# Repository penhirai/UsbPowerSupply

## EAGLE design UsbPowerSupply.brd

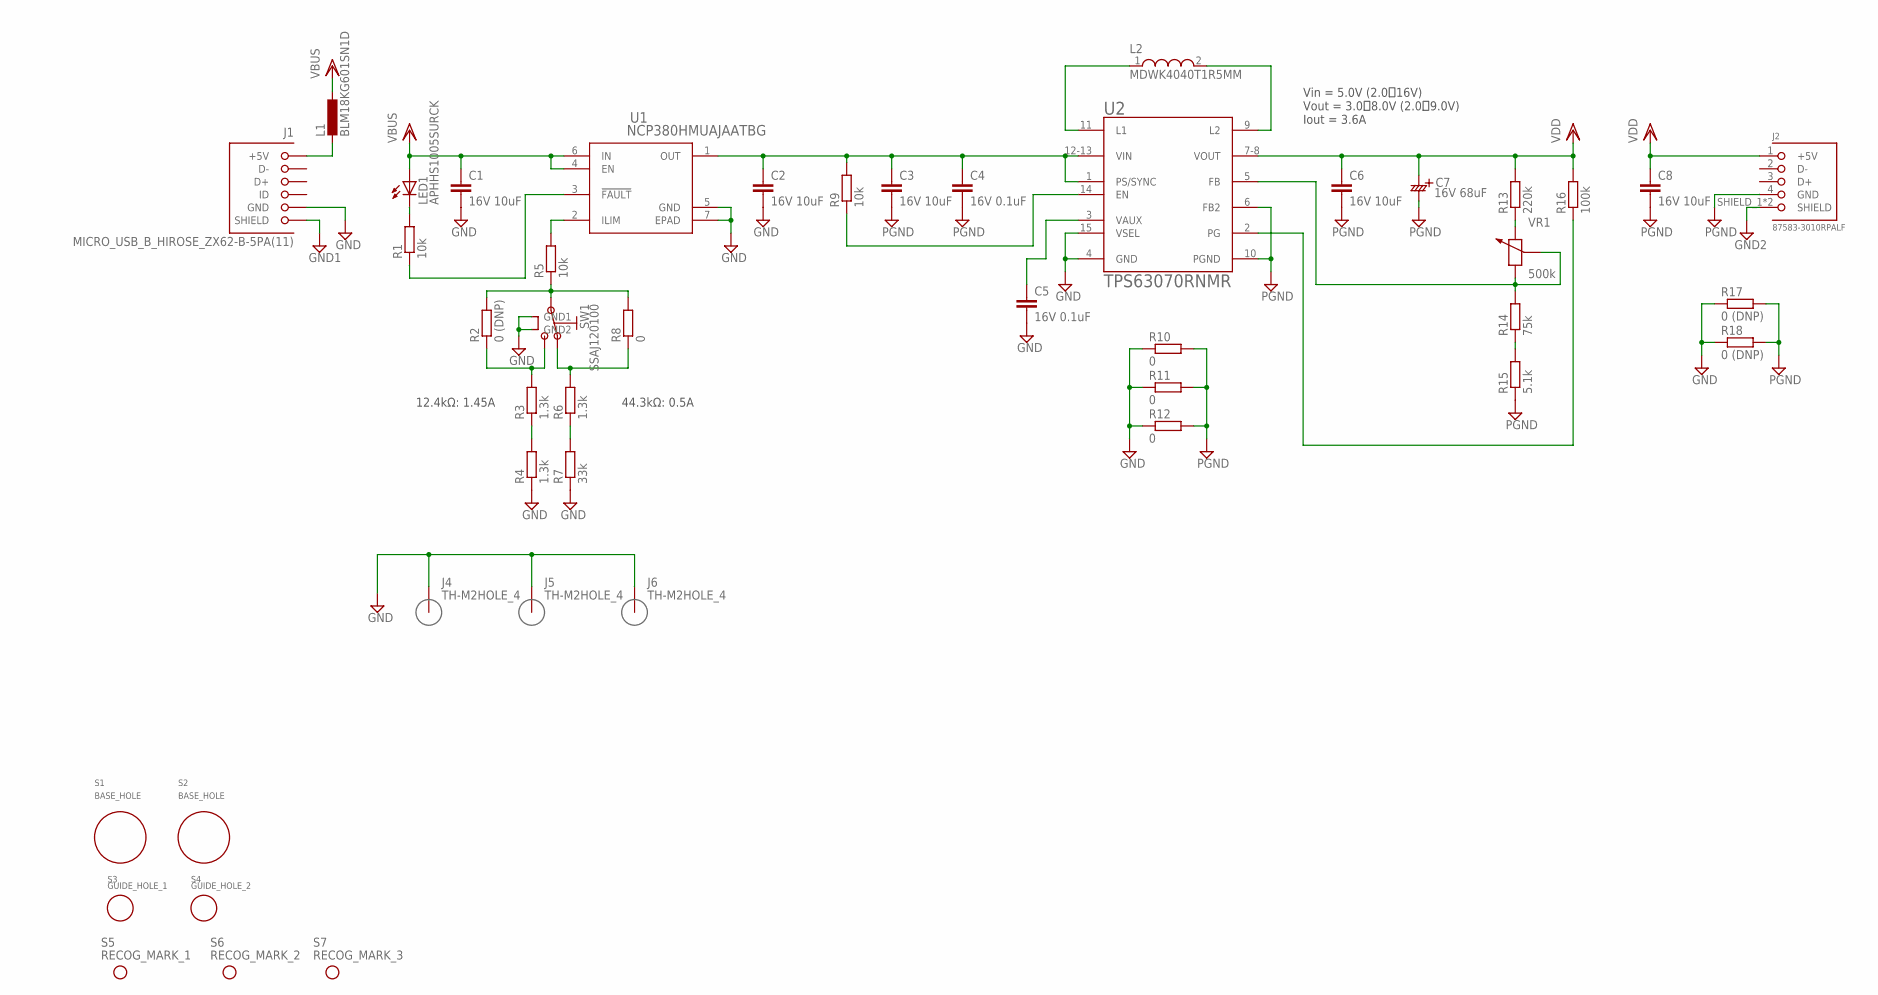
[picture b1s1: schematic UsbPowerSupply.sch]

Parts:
C1, C2, C3, C6, C8: 16V 10uF; C0603M
C4, C5: 16V 0.1uF; C0402M
C7: 16V 68uF; EEFCX_7343
J1: MICRO_USB_B_HIROSE_ZX62-B-5PA(11); USB_MICRO_B-HIROSE-ZX62-B-5PA(11)
J2: 87583-3010RPALF; USB_A_FEMALE
J4, J5, J6: TH-M2HOLE_4; HOLE_M2_PHI4
L1: BLM18KG601SN1D; L1608
L2: MDWK4040T1R5MM; WE-MAPI_4020
LED1: APHHS1005SURCK; 1005
R1, R5, R9: 10k; R0402R
R2, R17, R18: 0 (DNP); R0402R
R3, R4, R6: 1.3k; R0402R
R7: 33k; R0402R
R8, R10, R11, R12: 0; R0402R
R13: 220k; R0402R
R14: 75k; R0402R
R15: 5.1k; R0402R
R16: 100k; R0402R
S1, S2: BASE_HOLE
S3: GUIDE_HOLE_1; GUIDE_HOLE
S4: GUIDE_HOLE_2; GUIDE_HOLE
S5: RECOG_MARK_1; RECOG_MARK
S6: RECOG_MARK_2; RECOG_MARK
S7: RECOG_MARK_3; RECOG_MARK
SW1: SSAJ120100
U1: NCP380HMUAJAATBG; NCP380_UDFN6
U2: TPS63070RNMR; QFN50P250X300X100-15N
VR1: 500k; VR_3006

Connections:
EN: R9.1, U2.14 (EN)
FB: R14.2, U2.5 (FB), VR1.2 (CENTER), VR1.3 (2)
GND: C1.2, C2.2, C5.2, J1.5 (GND), J4.P$1, J5.P$1, J6.P$1, R4.1, R7.1, R10.1, R11.1, R12.1, R17.1, R18.1, SW1.4 (GND1), SW1.5 (GND2), U1.5 (GND), U1.7 (EPAD), U2.4 (GND), U2.15 (VSEL)
GND1: J1.P$1 (SHIELD), J1.P$2 (SHIELD), J1.P$3 (SHIELD), J1.P$4 (SHIELD), J1.P$5 (SHIELD), J1.P$6 (SHIELD)
GND2: J2.SHIELD_1 (SHIELD), J2.SHIELD_2 (SHIELD)
L1: L2.1, U2.11 (L1)
L2: L2.2, U2.9 (L2)
unnamed: R14.1, R15.2
unnamed: J1.1 (+5V), L1.2
unnamed: LED1.K, R1.2
unnamed: R1.1, U1.3 (!FAULT)
unnamed: R5.2, U1.2 (ILIM)
unnamed: R2.2, R5.1, R8.2, SW1.2
unnamed: R13.1, VR1.1
unnamed: R3.1, R4.2
unnamed: R6.2, R8.1, SW1.3 (1)
unnamed: R2.1, R3.2, SW1.1 (3)
unnamed: R6.1, R7.2
PG: R16.1, U2.2 (PG)
PGND: C3.2, C4.2, C6.2, C7.MINUS, C8.2, J2.4 (GND), R10.2, R11.2, R12.2, R15.1, R17.2, R18.2, U2.6 (FB2), U2.10 (PGND)
VAUX: C5.1, U2.3 (VAUX)
VBUS: C1.1, L1.1, LED1.A, U1.4 (EN), U1.6 (IN)
VBUS2: C2.1, C3.1, C4.1, R9.2, U1.1 (OUT), U2.1 (PS/SYNC), U2.12-13 (VIN)
VDD: C6.1, C7.PLUS, C8.1, J2.1 (+5V), R13.2, R16.2, U2.7-8 (VOUT)

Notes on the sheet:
44.3kΩ: 0.5A
12.4kΩ: 1.45A
Vin = 5.0V (2.0～16V) Vout = 3.0～8.0V (2.0～9.0V) Iout = 3.6A

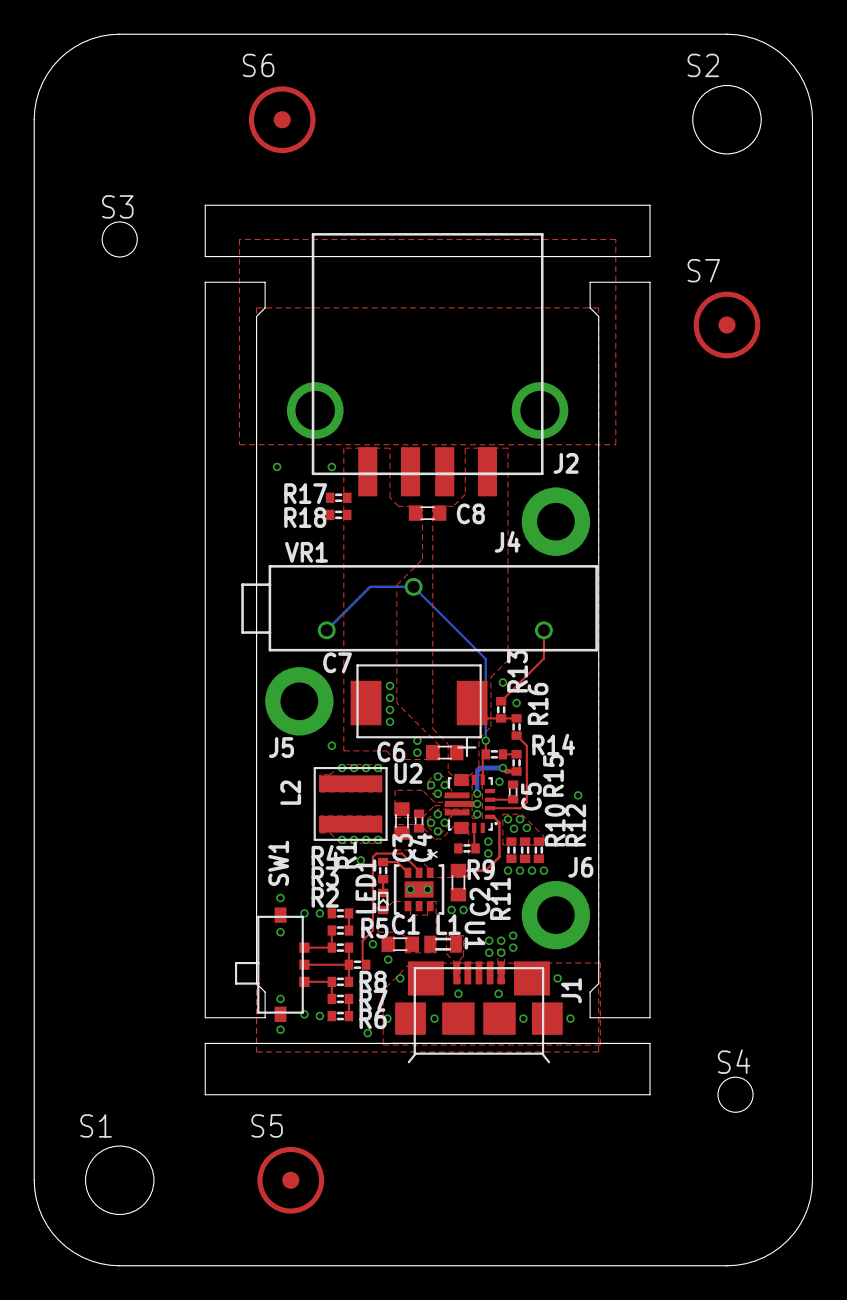
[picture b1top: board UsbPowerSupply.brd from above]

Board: 2 copper layers, 45.5 x 72.0 mm, 45 parts (0 on the bottom side), 24 nets.

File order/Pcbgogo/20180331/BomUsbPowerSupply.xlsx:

品名 Name | 部品番号 Designator | 個数 Quantity | 値 Value | パッケージ Package | 説明 Description | 部品メーカー Manufacturer | 部品メーカーの品番 Manufacturer Part Number | 実装 / 非実装ｼﾞｯｿｳﾋｼﾞｯｿｳ | 代替可否ﾀﾞｲﾀｲｶﾋ
抵抗ﾃｲｺｳ | R8, R10, R11, R12 | 4 | 0 | 1005 | RESISTOR, European symbol | KOA | RK73Z1ETTP | 実装ｼﾞｯｿｳ | 可ｶ
抵抗ﾃｲｺｳ | R2, R17, R18 | 3 | 0 | 1005 | RESISTOR, European symbol | KOA | RK73Z1ETTP | 非実装ﾋｼﾞｯｿｳ | 可ｶ
抵抗ﾃｲｺｳ | R3, R4, R6 | 3 | 1.3k | 1005 | RESISTOR, European symbol | KOA | RK73H1ETTP1301F | 実装ｼﾞｯｿｳ | 可ｶ
抵抗ﾃｲｺｳ | R16 | 1 | 100k | 1005 | RESISTOR, European symbol | KOA | RK73H1ETTP1003F | 実装ｼﾞｯｿｳ | 可ｶ
抵抗ﾃｲｺｳ | R1, R5, R9 | 3 | 10k | 1005 | RESISTOR, European symbol | KOA | RK73H1ETTP1002F | 実装ｼﾞｯｿｳ | 可ｶ
コンデンサ | C4, C5 | 2 | 16V 0.1uF | 1005 | CAPACITOR, European symbol | Murata | GRM155R71E104KE14J | 実装ｼﾞｯｿｳ | 不可ﾌｶ
コンデンサ | C1, C2, C3, C6, C8 | 5 | 16V 10uF | 1608 | CAPACITOR, European symbol | Taiyo Yuden | EMK107BBJ106MA-T | 実装ｼﾞｯｿｳ | 可ｶ
コンデンサ | C7 | 1 | 16V 68uF | 7343 |  | Panasonic | EEF-CX1C680R | 実装ｼﾞｯｿｳ | 不可ﾌｶ
抵抗ﾃｲｺｳ | R13 | 1 | 220k | 1005 | RESISTOR, European symbol | KOA | RK73H1ETTP2203F | 実装ｼﾞｯｿｳ | 可ｶ
抵抗ﾃｲｺｳ | R7 | 1 | 33k | 1005 | RESISTOR, European symbol | KOA | RK73H1ETTP3302F | 実装ｼﾞｯｿｳ | 可ｶ
抵抗ﾃｲｺｳ | R15 | 1 | 5.1k | 1005 | RESISTOR, European symbol | KOA | RK73H1ETTP5101F | 実装ｼﾞｯｿｳ | 可ｶ
可変抵抗ｶﾍﾝﾃｲｺｳ | VR1 | 1 | 500k | スルーホール |  | Bourns | 3006P-1-504LF | 実装ｼﾞｯｿｳ | 可ｶ
抵抗ﾃｲｺｳ | R14 | 1 | 75k | 1005 | RESISTOR, European symbol | KOA | RK73H1ETTP7502F | 実装ｼﾞｯｿｳ | 可ｶ
USB コネクタ（A レセプタクル） | J2 | 1 | ー | SMD |  | CNC Tech | 1001-002-01100 | 実装ｼﾞｯｿｳ | 可ｶ
LED | LED1 | 1 | ー | 1005 |  | Kingbright | APHHS1005SURCK | 実装ｼﾞｯｿｳ | 不可ﾌｶ
基準穴ｷｼﾞｭﾝｱﾅ | S1, S2 | 2 | ー | ー | BASE_HOLE | ー | ー | ー
インダクタ | L1 | 1 | ー | 1608 | INDUCTOR, European symbol | Murata | BLM18KG601SN1D | 実装ｼﾞｯｿｳ | 不可ﾌｶ
ガイド穴ｱﾅ | S3 | 1 | ー | ー | GUIDE_HOLE_1 | ー | ー | ー
ガイド穴ｱﾅ | S4 | 1 | ー | ー | GUIDE_HOLE_2 | ー | ー | ー
インダクタ | L2 | 1 | ー | 4020 | SMD Metal Alloy Power Inductor | Taiyo Yuden | MDWK4040T1R5MM | 実装ｼﾞｯｿｳ | 不可ﾌｶ
USB コネクタ（microB レセプタクル） | J1 | 1 | ー | SMD | Connector Receptacle USB - micro B 2.0 5 Position Surface Mount, Right Angle, H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 | Hirose | ZX62-B-5PA(33) | 実装ｼﾞｯｿｳ | 不可ﾌｶ
電源スイッチ ICﾃﾞﾝｹﾞﾝ | U1 | 1 | ー | UDFN6 |  | On Semiconductor | NCP380HMUAJAATBG | 実装ｼﾞｯｿｳ | 不可ﾌｶ
認識マークﾆﾝｼｷ | S5 | 1 | ー | ー | RECOG_MARK_1 | ー | ー | ー
認識マークﾆﾝ | S6 | 1 | ー | ー | RECOG_MARK_2 | ー | ー | ー
認識マークﾆﾝ | S7 | 1 | ー | ー | RECOG_MARK_3 | ー | ー | ー
スイッチ | SW1 | 1 | ー | SMD |  | Alps | SSAJ120100 | 実装ｼﾞｯｿｳ | 不可ﾌｶ
スルーホール | J4, J5, J6 | 3 | ー | ー | スルーホールφ2 | ー | ー | ー
電源 ICﾃﾞﾝｹﾞﾝ | U2 | 1 | ー | 15-VQFN-HR | Wide Input Voltage (2V-16V) Buck-Boost Converter 15-VQFN-HR | Texas Instruments | TPS63070RNMR | 実装ｼﾞｯｿｳ | 不可ﾌｶ

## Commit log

2018-08-14 新規作成

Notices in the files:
parts and their libraries:
Wurth_Elektronik_Passive_rev15f: Copyright: Würth Elektronik
